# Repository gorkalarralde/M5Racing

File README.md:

# M5Racing
## M5Stack DAS Racing description:

M5Racing (M5R) is a new Data Acquisition System (DAS) for any type of vehicle (cars, motorcycles, bikes, etc.). It provides data sampling, revision (on a small integrated GUI screen or an optional, 5" external display) and logging (when needed).

This new Racing Data Logger is based on the M5Stack modular system. The M5Stack Core Base development board is highly efficient and includes an industrial grade case, an ESP32 with 16MB of flash memory and Bluetooth communication.

The main advantage is the powerful modular system provided by the M5Stack design, which means you only have to get the modules and sensors you need for achieving your objectives. For example, if you only need TTPMS and some OBD-II ECU data, no modules have to be installed, given that Bluetooth connectivity is ready to use in the base M5Stack Core.

- Data Acquisition System (DAS) and Analysis for car and motorcycle racing.
- Telemetry and data logging for all installed sensors and vehicle ECU data.
- 2.0-inch, 320x240 Colour TFT LCD, with a maximum brightness of 853 nit.
- GUI for browsing through data and config menus.
- ESP32 (two low-power Xtensa® 32-bit LX6 microprocessors at 240 MHZ, dual core, 600 DMIPS).
- Dual Bluetooth (classic BT 3.0 and BLE 4.0) with 2.4-GHz 3D Antenna.
- FreeRTOS firmware and 16MB of flash memory.
- On-track engineering, with LIVE sensor reading.
- Easy FIRMWARE upgrade through new "firmware.bin" releases.
- Based on the M5Stack Core: 
  - Option 1: https://docs.m5stack.com/en/core/basic_v2.6 (most economical option).
  - Option 2: https://docs.m5stack.com/en/core/gray (another valid option).
- The log files that are created can be opened with: 
  - RaceRender by HP Tuners, which creates a Data-Overlay video (WIN and MAC / freeware).
  - https://serious-racing.com (cloud only / freeware).
  - RaceChrono Pro data analysis with sync video (Android / iOs, 23 euros per license).
  - Circuit Tools by RaceLogic VBOX and data analysis with sync video (WIN and MAC / freeware).
  - DashWare by GoPro, which creates a Data-Overlay video (WIN / freeware).
  - Race Studio 3 by AIM (WIN / freeware).
  - MS Excel or similar data spreadsheets or txt (WIN and MAC / freeware).
  - i2 Standard by Motec (WIN / freeware).

A list of the modules, sensor units and special installation processes that are needed for the multiple functionalities of M5R is shown below.

## M5R Full Technical Data Specs: 

- 16 GB microSD CARD STORAGE
  - Up to 16GB FAT32 formatted microSD TF cards
  - Creates compatible UTF-8 .CSV format files
  - Compatibility with almost any data analysis program
  - Unlimited session length, ideal for 24-hour races

- 10 Hz GPS DATA
  - GPS data 10 times per second for: 
    - automatic lap timer
    - automatic on-track recognition (more than 1000 tracks available)
    - accurate track paths for every curve
    - accurate time and date
    - also altitude and speed data

- 50 Hz DATA LOGGING
  - Logging 50 times per second (every 20 ms) 
  - High-speed data sampling for high variable data sensors such as: 
    - Suspension
    - G-forces
    - IR temps (tires and brakes)

- OBD-II ECU DATA
  - Classic Bluetooth 3.0 connection
  - Requires an OBD-II-to-BT 3.0 dongle with a compatible ELM327 chipset (Version 1.5 or higher) and 2.1 software
  - Also BT 2.0 and BT 4.0: compatibility depends on the vehicle and the OBD-II-to-BT dongle used
  - ECU Engine RPM
  - SHIFT-light indicator
  - ECU SPEED data
  - Actual GEAR
  - ECU throttle position sensor data (TPS)
  - Coolant temp (with On-screen alert if temp > 106º C)
- TTPMS DATA
  - Inside tire temperature and pressure monitoring system
  - BLE Bluetooth 4.0 connection with open data TTPMS sensors
  - Up to 1 sample per second (1 Hz) if sensor data changes rapidly
  - Includes on-screen alerts for tire pressure that is too low (20 PSI) or too high
  - Includes easy "check-by-colour" for optimum or out-of-range values
  - 2 options: 
    - Internal (real TTPMS, but requires installation): 
      - https://amzn.eu/d/5TqwCvm
      - https://amzn.eu/d/ecVz5fE
    - External (very easy install, but temperature is ambient temp): 
      - https://amzn.eu/d/6uYdyAY
      - https://amzn.eu/d/dzelCKM
      - https://amzn.eu/d/eoFtA7H
- TIRE TEMPERATURES
  - 3-zone or 8-zone expanded data sampling to choose from
  - Based on external infrared (IR) sensors (from -40º to 380º C)
  - Includes "check-by-colour" values and alerts for temperature too low or too high (> 100º C)
  - Simplified on-screen data analysis: 
    - Outside, middle and inside temps for each tire 
    - At setup, includes camber tips for optimum performance
    - Left, centre and right temps for each motorcycle (bike) tire
- ENVIRONMENTAL DATA
  - Ambient light (Lux)
  - Ambient temperature (º C)
  - Ambient pressure (BAR)
  - Ambient humidity (%)
  - Includes alerts for ambient temp too low or too high: 
    - Below 5º C
    - Above 32º C
- G-SENSORS and 9-axis IMU
  - LEAN angle (especially useful for motorcycle riders and bikers)
  - YAW or rotation angle to detect under/over steering of a vehicle
  - Includes PITCH angle for live rake sampling
  - Longitudinal acceleration: 
    - Under braking (negative G-values)
    - Throttling (positive G-values)
  - Lateral acceleration: 
    - Cornering forces
- ROTOR and CALIPER TEMPERATURE
  - Based on external infrared (IR) sensors
  - Includes alerts for rotor values that are too low or too high
    - Below 100º C (cold)
    - Above 600º C (overheated)
  - Includes alerts for too-high caliper values 
    - Above 180º C (overheated / risk of vaporisation)
- STEERING ANGLE
- THROTTLE POSITION SENSOR
  - Only needed if OBD-II BT is not in use: 
    - Car: a ToF sensor must be installed under the throttle lever
    - Motorcycle: an angle sensor must be installed inside the throttle
- SUSPENSION TRAVEL AND SAG ADJUSTMENT
  - Measures the suspension travel for each wheel
  - Includes easy SAG adjustment process: 
    - 3-step guide with description and images
    - With "check-by-colour" for optimum calculated values
    - Also includes LIVE SAG for on-track setup
  - Includes alerts for: 
    - Near-bottoming alert (if less than 10 mm of travel left): the front dives too much while braking
    - Poor SAG
- AUTO POWER SHIFTER (APS)
  - Only for models equipped with UP/DOWN shifter (UP-Shifter and Blipper)
  - Requires an active OBD-II-to-BT 3.0 or 4.0 dongle 
  - Completely tuneable with 4 riding modes: 
    - ECO, STREET, SPORT and TRACK
    - Each mode completely configurable for UP RPM and DOWN RPM, for each gear!!!
    - Not only FULL AUTO but also a FULL MANUAL UP/DOWN gear selector in any mode
  - For more convenient MODE selection and AUTO/MANUAL APS UP/DOWN gear selection, one of these 5-button controls is needed: 
    - https://amzn.eu/d/10rhYnT
    - https://amzn.eu/d/iwBvQux
- BRAKE PRESSURE SENSOR(S)
  - Brake sensor with 2 options and functionalities: 
    - ON/OFF: only senses if you do or don’t brake via brake light activation
    - Proper pressure gauge(s): samples exact pressure at each brake lever (requires installation and bleeding of new brake line hoses)
- 7" or 5" HMI REALTIME DASHBOARD
  - 7-inch or 5-inch 800x480 touchscreen monitor with: 
    - Racing Dashboard design
    - A 24 or smaller 18-LED strip that shows the actual RPM with colour ramping
    - SHIFT-light indicator (all LEDs flash in bright white), completely synchronised with the APS
    - Shows all of the vehicle’s LIVE data and sensors
    - GUI design better than the M5Stack Core alone, with multiple graphic screens
    - Information management
    - Browsing through the configuration menus
    - Adaptative brightness to actual ambient light (lux)
    - Shows alarms and alerts: 
      - GPS signal alert
      - TTPMS alarm
      - Coolant alarm
      - Ambient temperature alert
      - TTPMS out of range alerts

## Required Modules, sensors and installation

 - 16GB microSD CARD STORAGE -> No special module needed (M5Stack Core included functionality)
 - 10 Hz GPS DATA
 - 50 Hz DATA LOGGING -> No special module needed (M5Stack Core included functionality)
 - OBD II ECU DATA -> No special module needed (M5Stack Core included functionality) 
 - TTPMS DATA -> No special module needed (M5Stack Core included functionality)
 - IR TIRE TEMPERATURES
 - ENVIRONMENTAL DATA -> No special module needed (M5Stack Core included functionality)
 - G-SENSORS and 9-axis IMU
 - ROTOR and CALIPER TEMPERATURE
 - STEERING ANGLE -> No special module needed (M5Stack Core included functionality)
 - THROTTLE POSITION SENSOR -> No special module needed (M5Stack Core included functionality) 
 - SUSPENSION TRAVEL AND SAG ADJUSTMENT
 - AUTO POWER SHIFTER (APS)
 - BRAKE PRESSURE SENSOR -> No special module needed (M5Stack Core included functionality)
 - 5" HMI REALTIME DASHBOARD

If I have seen further than others, it is by standing upon the shoulders of giants:

- Luis Sáenz (luissaenz1987@gmail.com) for 3D CAD and Prototyping.
- Fermín (now.pcb.now@gmail.com) for PCB Design and Prototyping.

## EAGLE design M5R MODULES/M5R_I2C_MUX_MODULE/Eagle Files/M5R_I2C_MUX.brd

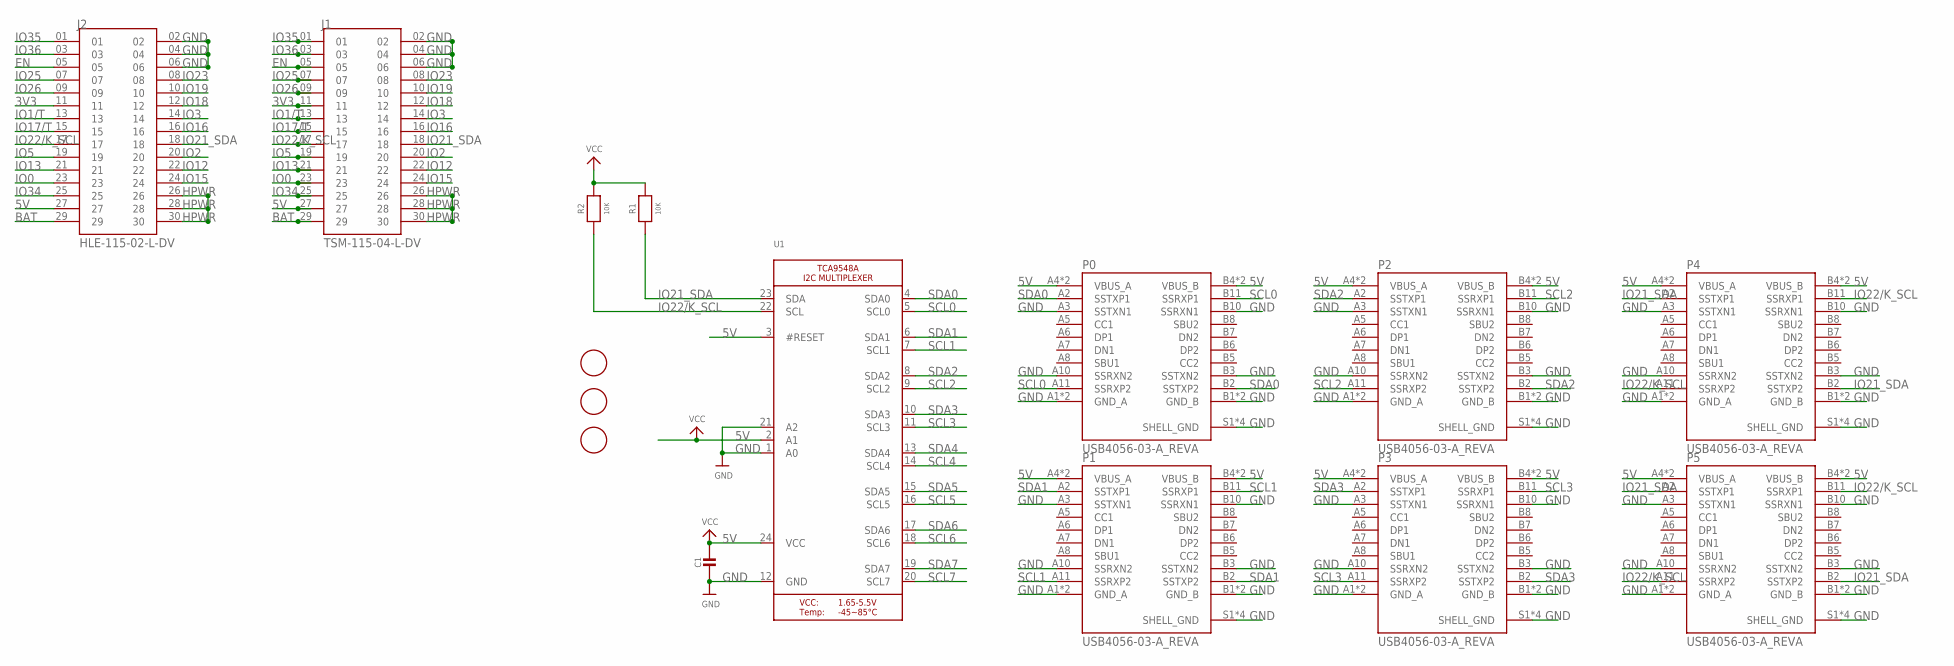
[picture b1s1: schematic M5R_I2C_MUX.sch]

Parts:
C1: CAP_CERAMIC0805-NOOUTLINE; 0805-NO
J1: TSM-115-04-L-DV; SAMTEC_TSM-115-04-L-DV
J2: HLE-115-02-L-DV; SAMTEC_HLE-115-02-L-DV
P0, P1, P2, P3, P4, P5: USB4056-03-A_REVA; GCT_USB4056-03-A_REVA
R1, R2: 10K; 0805
U1: TCA9548A; TSSOP24
U$3, U$4, U$5: FIDUCIAL; FIDUCIAL_1MM

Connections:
3V3: J1.11, J2.11
5V: C1.1, J1.27, J2.27, P0.A4 (VBUS_A), P0.A9 (VBUS_A), P0.B4 (VBUS_B), P0.B9 (VBUS_B), P1.A4 (VBUS_A), P1.A9 (VBUS_A), P1.B4 (VBUS_B), P1.B9 (VBUS_B), P2.A4 (VBUS_A), P2.A9 (VBUS_A), P2.B4 (VBUS_B), P2.B9 (VBUS_B), P3.A4 (VBUS_A), P3.A9 (VBUS_A), P3.B4 (VBUS_B), P3.B9 (VBUS_B), P4.A4 (VBUS_A), P4.A9 (VBUS_A), P4.B4 (VBUS_B), P4.B9 (VBUS_B), P5.A4 (VBUS_A), P5.A9 (VBUS_A), P5.B4 (VBUS_B), P5.B9 (VBUS_B), R1.2, R2.2, U1.2 (A1), U1.3 (#RESET), U1.24 (VCC)
BAT: J1.29, J2.29
EN: J1.05, J2.05
GND: C1.2, J1.02, J1.04, J1.06, J2.02, J2.04, J2.06, P0.A1 (GND_A), P0.A3 (SSTXN1), P0.A10 (SSRXN2), P0.A12 (GND_A), P0.B1 (GND_B), P0.B3 (SSTXN2), P0.B10 (SSRXN1), P0.B12 (GND_B), P0.S1 (SHELL_GND), P0.S2 (SHELL_GND), P0.S3 (SHELL_GND), P0.S4 (SHELL_GND), P1.A1 (GND_A), P1.A3 (SSTXN1), P1.A10 (SSRXN2), P1.A12 (GND_A), P1.B1 (GND_B), P1.B3 (SSTXN2), P1.B10 (SSRXN1), P1.B12 (GND_B), P1.S1 (SHELL_GND), P1.S2 (SHELL_GND), P1.S3 (SHELL_GND), P1.S4 (SHELL_GND), P2.A1 (GND_A), P2.A3 (SSTXN1), P2.A10 (SSRXN2), P2.A12 (GND_A), P2.B1 (GND_B), P2.B3 (SSTXN2), P2.B10 (SSRXN1), P2.B12 (GND_B), P2.S1 (SHELL_GND), P2.S2 (SHELL_GND), P2.S3 (SHELL_GND), P2.S4 (SHELL_GND), P3.A1 (GND_A), P3.A3 (SSTXN1), P3.A10 (SSRXN2), P3.A12 (GND_A), P3.B1 (GND_B), P3.B3 (SSTXN2), P3.B10 (SSRXN1), P3.B12 (GND_B), P3.S1 (SHELL_GND), P3.S2 (SHELL_GND), P3.S3 (SHELL_GND), P3.S4 (SHELL_GND), P4.A1 (GND_A), P4.A3 (SSTXN1), P4.A10 (SSRXN2), P4.A12 (GND_A), P4.B1 (GND_B), P4.B3 (SSTXN2), P4.B10 (SSRXN1), P4.B12 (GND_B), P4.S1 (SHELL_GND), P4.S2 (SHELL_GND), P4.S3 (SHELL_GND), P4.S4 (SHELL_GND), P5.A1 (GND_A), P5.A3 (SSTXN1), P5.A10 (SSRXN2), P5.A12 (GND_A), P5.B1 (GND_B), P5.B3 (SSTXN2), P5.B10 (SSRXN1), P5.B12 (GND_B), P5.S1 (SHELL_GND), P5.S2 (SHELL_GND), P5.S3 (SHELL_GND), P5.S4 (SHELL_GND), U1.1 (A0), U1.12 (GND), U1.21 (A2)
HPWR: J1.26, J1.28, J1.30, J2.26, J2.28, J2.30
IO0: J1.23, J2.23
IO1/T: J1.13, J2.13
IO2: J1.20, J2.20
IO3: J1.14, J2.14
IO5: J1.19, J2.19
IO12: J1.22, J2.22
IO13: J1.21, J2.21
IO15: J1.24, J2.24
IO16: J1.16, J2.16
IO17/T: J1.15, J2.15
IO18: J1.12, J2.12
IO19: J1.10, J2.10
IO21_SDA: J1.18, J2.18, P4.A2 (SSTXP1), P4.B2 (SSTXP2), P5.A2 (SSTXP1), P5.B2 (SSTXP2), R1.1, U1.23 (SDA)
IO22/K_SCL: J1.17, J2.17, P4.A11 (SSRXP2), P4.B11 (SSRXP1), P5.A11 (SSRXP2), P5.B11 (SSRXP1), R2.1, U1.22 (SCL)
IO23: J1.08, J2.08
IO25: J1.07, J2.07
IO26: J1.09, J2.09
IO34: J1.25, J2.25
IO35: J1.01, J2.01
IO36: J1.03, J2.03
SCL0: P0.A11 (SSRXP2), P0.B11 (SSRXP1), U1.5 (SCL0)
SCL1: P1.A11 (SSRXP2), P1.B11 (SSRXP1), U1.7 (SCL1)
SCL2: P2.A11 (SSRXP2), P2.B11 (SSRXP1), U1.9 (SCL2)
SCL3: P3.A11 (SSRXP2), P3.B11 (SSRXP1), U1.11 (SCL3)
SCL4: U1.14 (SCL4)
SCL5: U1.16 (SCL5)
SCL6: U1.18 (SCL6)
SCL7: U1.20 (SCL7)
SDA0: P0.A2 (SSTXP1), P0.B2 (SSTXP2), U1.4 (SDA0)
SDA1: P1.A2 (SSTXP1), P1.B2 (SSTXP2), U1.6 (SDA1)
SDA2: P2.A2 (SSTXP1), P2.B2 (SSTXP2), U1.8 (SDA2)
SDA3: P3.A2 (SSTXP1), P3.B2 (SSTXP2), U1.10 (SDA3)
SDA4: U1.13 (SDA4)
SDA5: U1.15 (SDA5)
SDA6: U1.17 (SDA6)
SDA7: U1.19 (SDA7)

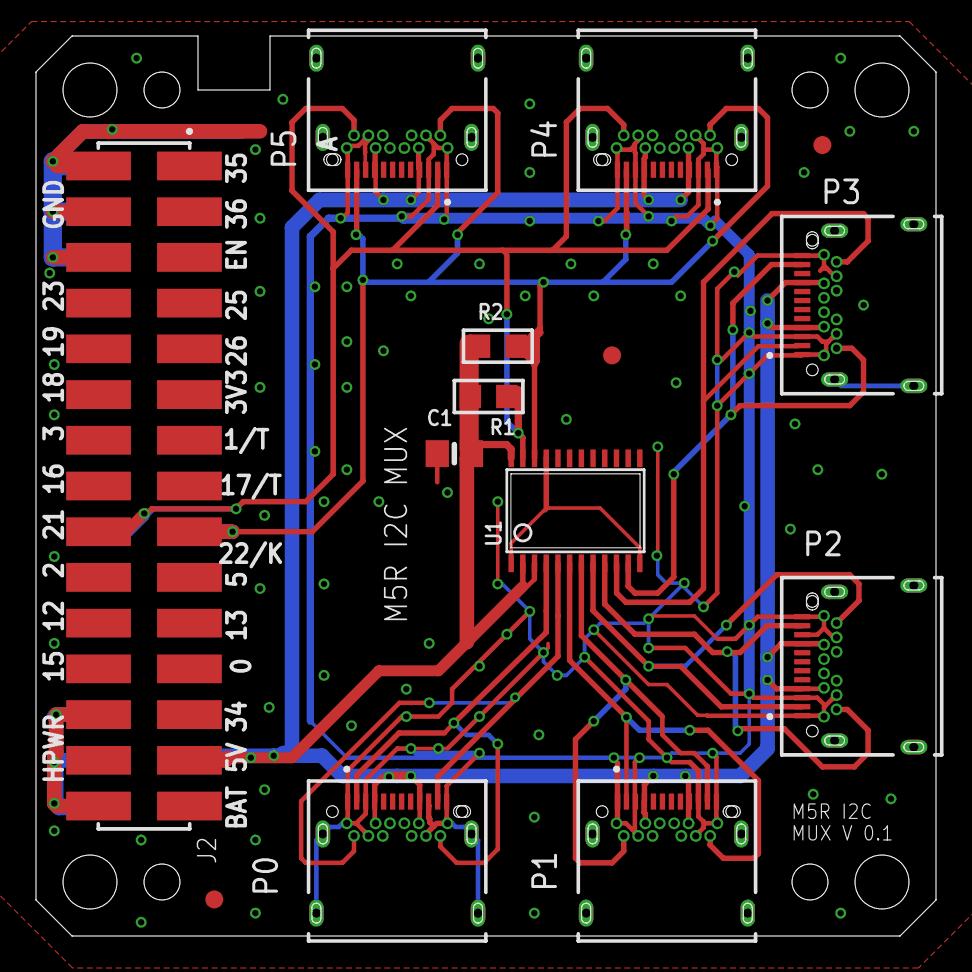
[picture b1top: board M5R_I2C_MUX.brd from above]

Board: 2 copper layers, 50.0 x 50.0 mm, 15 parts (1 on the bottom side), 34 nets.

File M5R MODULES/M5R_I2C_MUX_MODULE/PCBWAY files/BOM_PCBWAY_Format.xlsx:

Item # | *Designator | *Qty | Manufacturer | *Mfg Part # | Description / Value | *Package/Footprint | Type | Your Instructions / Notes | Pins
1 | J1 | 1 | Samtec Inc. | TSM-115-04-L-DV | Connector Header Surface Mount 30 position 0.100" (2.54mm) 3.05mm post height | SAMTEC_TSM-115-04-L-DV | SMD |  | 30
2 | U1 | 1 | Texas Instruments | TCA9548APWR | Bus Switch 1 x 8:1 24-TSSOP | TSSOP24 | SMD |  | 24
3 | R1,R2 | 2 | TE Connectivity Passive Product | 2176093-5 | 10 kOhms ±0.1% 0.25W, 1/4W Chip Resistor 0805 (2012 Metric) Thin Film | 0805 (2012 Metric) | SMD |  | 2
4 | C1 | 1 | Vishay Sprague | TMCP1D104MTRF | 0.1 µF Molded Tantalum Capacitors 20 V 0805 (2012 Metric) 33Ohm @ 100kHz | 0805 (2012 Metric) | SMD |  | 2
5 | P0,P1,P2,P3,P4,P5 | 6 | GCT | USB4056-03-A | USB-C (USB TYPE-C) USB 3.2 Gen 2 (USB 3.1 Gen 2, Superspeed + (USB 3.1)) Recept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 | SMD; Through Hole | SMD/Through Hole |  | 28
6 | J2 | 1 | Samtec Inc. | HLE-115-02-L-DV | Connector Header Receptacle Surface Mount 30 position 0.100" (2.54mm) | SAMTEC_HLE-115-02-L-DV | SMD |  | 30

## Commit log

2022-10-20 Create LICENSE
